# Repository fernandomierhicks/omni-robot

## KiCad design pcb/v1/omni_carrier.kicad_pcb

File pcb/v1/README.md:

# pcb/v1: Teensy 4.1 carrier (schematic draft, for review)

A two-layer breakout for the robot's Teensy 4.1: every header pin to a JST XH connector (2–6 pins), the CAN
transceivers as plug-in modules, and only the few parts a bare breakout can't do without. **Status (Nov 17): rev C
schematic for review; board placement study, not routed.** Every part is through-hole (Fernando solders by hand). Target fab:
OSH Park 2-layer (6 mil trace/space, 13 mil drill, 7 mil annular ring, 1.6 mm, ENIG, $5 per square inch for three).
How the board sits in the robot: [robot_block_diagram.html](robot_block_diagram.html) (published as an artifact).

| File | What |
| --- | --- |
| `tools/gen_sch.py` | **The source.** Generates the schematic, the project's symbol/footprint libraries and `nets.json` (the intended connectivity). Edit this, not the sheet, until the schematic is approved; after that KiCad is the source |
| `tools/check.py` | KiCad ERC; KiCad's netlist against `nets.json`; every Teensy pin against `firmware/lib/omni_fw/board_teensy41.h` (and the firmware changes this board needs); the review PDF |
| `omni_carrier.kicad_sch` / `.kicad_pro` | Open in KiCad 10 |
| `omni_carrier.kicad_sym`, `omni_carrier.pretty/` | Teensy 4.1 (outer 48 pins) and the SN65HVD230 module; the Teensy's 2 × 1x24 socket footprint, the Ø12 buzzer's (slotted pin 2) and J5's (1x4 socket + the ELRS receiver's outline and model) |
| `tools/elrs_model.py` → `models/elrs_receiver_on_J5.step` | The ELRS receiver on its male header, with its U.FL plug and T antenna, in J5's 3D frame (sizes from the vendor's pictures: VERIFY) |
| `tools/buzzer_model.py` → `models/buzzer_12085.step` | BZ1's 12085 buzzer (Ø12 × 8.5) in its footprint's 3D frame |
| `models/teensy_4_1.step`, `models/can.step`; `tools/paint_models.py` → `*_colour.step` | Fernando's Teensy 4.1 and SN65HVD230 module models (copied from `cad/v16/reference/electronics`, his SolidWorks parts; no colours), and the painted copies the footprints use |
| `tools/colour_step.py` → `out/omni_carrier_colour.step` | **The board for the CAD:** KiCad's STEP export, every face coloured (see Board, STEP) |
| `out/omni_carrier_schematic.pdf` | The sheet for review (A2) |
| `tools/gen_pcb.py` | Places the footprints on `omni_carrier.kicad_pcb` (placement study; runs in KiCad's Python) |
| `robot_block_diagram.html` | The whole robot's power and signal block diagram |

```powershell
cd pcb/v1
& $env:USERPROFILE\.venvs\omni-robot-sim\Scripts\python.exe tools/gen_sch.py
& $env:USERPROFILE\.venvs\omni-robot-sim\Scripts\python.exe tools/check.py    # ERC 0, netlist = intent, firmware pins
```

## The robot around it (Fernando, Nov 17)

- **One main switch, which is also the e-stop**, right before the 30 A fuse: it cuts the whole robot, the computer
  and the Teensy included. There is no separate e-stop circuit, no contactor and no power board: the converters
  (19 V, 12 V, 5 V) are discrete DC/DC modules, and the four AK40-10s take the pack directly with no fuses of their
  own (they limit their own current).
- **One common ground** in the robot; CAN carries no ground wire.
- **USB:** the BMAX B8A Pro's four A and one C ports are all taken without a hub (D435, Teensy, servo adapter, lidar
  adapter, mic), and the GMKtec M5 Ultra has fewer. Proposed: a powered USB 2 hub on the 5 V rail for the lidar adapter,
  the mic and the servo adapter (plus spares); the D435 (USB 3) and the Teensy keep direct ports.

## Design (rev C)

- **Power: the Teensy runs from USB only.** +5V on the connectors is the Teensy's VIN (= VUSB, trace intact); +3V3 is
  its regulator (~250 mA for the BNO085, the CAN modules ≤ 20 mA each, the 3V3 LED and the spares).
- **Through-hole only:** standing 1/4 W resistors (2.54 mm pitch), disc and radial capacitors, a 2N7000 (TO-92), a
  1N4148 (DO-35), a 3 mm LED; the Teensy (2 × 1x24) and the CAN modules (1x6) in 0.1 in sockets.
- **CAN1 (J6: H, L):** the AK40-10s are daisy-chained in the harness. The SN65HVD230 module (U2, `components/can`;
  pins 3V3, GND, CTX, CRX, CANH, CANL) carries its own 120 Ω, terminating this end; **the far end of the chain needs
  the second 120 Ω** (harness or last motor). **CAN3 (J10: H, L):** reserved payload bus, U3 fitted when used.
- **IMU, the BNO085 board in `components/imu`:** J4 = VCC, GND; J3 = SCL, SDA, AD0, CS, INT, RST in the board's own
  order, so the cable runs straight. In SPI mode SCL is SCK (13), SDA is MISO (12), AD0 is MOSI (11) (BNO08x pin
  functions; VERIFY on the board). PS0/PS1 are tied high on the board; BOOTN is not wired.
- **Pack voltage: the INA226 (Nov 19, Fernando).** No divider on the board any more (it was J1 + 100k/10k on A17): the
  INA226 already sits on the pack's high side after the fuse, and its bus-voltage register reads the pack (0-36 V,
  1.25 mV steps, better than the divider through the Teensy's ADC). Pin 41 (A17) is a spare on J19. The 21 V stop now
  depends on I2C, so the firmware must treat a missing or stale INA226 reading as a low pack (fail safe). VERIFY on
  the module bought that its VBUS pin sees the pack (on some INA226 boards VBUS is tied to IN−, on others it is a
  separate pin to wire to it).
- **Buzzer (BZ1, on the board, Nov 18):** a 12085 passive magnetic buzzer (Ø12 × 8.5 mm, 42 Ω, 5 V;
  `components/buzzer`) soldered straight to the carrier, no lead. 2N7000 low-side switch with a 1N4148 flyback to
  +5V; firmware `tone()` drives it (a passive buzzer needs the square wave). About 120 mA peak from USB 5 V, ~60 mA
  average while sounding. Footprint `omni_carrier:Buzzer_D12_P6.5-7.6_Slot`: pin 1 = + (square pad, marked +), pin 2
  in a plated slot that takes either common pin pitch (6.5 or 7.6 mm). **VERIFY the pitch and + mark on the
  delivered buzzers.** The 2N7000 at 3.3 V gate is near its threshold; if the buzzer is quiet, swap Q1 for a
  logic-level TO-92 FET.
- **RGB status LED (J15: R, GND, G, B, Nov 18):** common cathode, driven straight from pins 28 (R), 29 (G), 5 (B)
  through the board's 330 / 100 / 100 Ω (~4 mA each at 3.3 V; VERIFY brightness on the LED chosen). J15 is in the
  LED's own leg order (R, cathode = the longest leg, G, B), so the LED can solder straight into J15's holes instead of
  the XH (2.50 vs 2.54 mm: 0.12 mm over the four legs) or sit on a lead. VERIFY the leg order on the LED bought.
- **NeoPixel strip (J20: +5V, DIN, GND):** driven straight from pin 35 (Serial8 TX, so WS2812Serial can update it
  without blocking the 1 kHz loop) through 330 Ω; Fernando has run strips on 3.3 V data. +5V here is USB, so short
  strips only (~10 pixels at modest brightness); a longer strip takes 5 V from the 5 V converter at the strip and only
  DIN + GND from here.
- **ELRS receiver (J5, on the board, Nov 18, Fernando):** the HPXGRC ELRS 2.4 GHz receiver
  (`components/radio receiver`: 20 × 11 mm, 0.8 g, four pads T R V G on one short edge, a U.FL and a 40 mm T
  antenna) plugs straight into the carrier, no lead: a straight male 1x4 header soldered into its pads (short pins
  up through the pads, the plastic under it) goes into **J5, a 1x4 2.54 mm female socket**. The receiver lies flat
  along the top edge, components up, 11 mm over the board (socket 8.5 + the header's plastic 2.5), its U.FL toward
  −x; nothing is placed under it (its outline is in J5's courtyard). Read from the G end its pads are G, V, R, T =
  J5's 1-4 (GND, 5 V, its RX ← Teensy TX2 (8), its TX → Teensy RX2 (7)). Footprint
  `omni_carrier:ELRS_Rx_Socket_1x04_P2.54mm` carries KiCad's socket model and the receiver's
  (`models/elrs_receiver_on_J5.step`, from `tools/elrs_model.py`). **VERIFY before ordering, with calipers: the pads'
  pitch (the vendor's pictures read 2.3-2.45 mm; a 2.54 header needs 2.54) and that the pads are plated through.**
  If they are not, the fallback is the receiver's own pre-soldered leads crimped into a 1x4 Dupont housing on the
  same socket. The antenna's 40 mm coax stands up from the U.FL in the CAD; route it upright, away from the computer
  and the converters.
- **Power monitors on I2C (pins 18/19):** J12 to the INA3221, J21 to the INA226, same bus; the modules' own pull-ups
  serve it. Both sit with the converters, on cables, so no rail current crosses the carrier.
- **Spares (J11, J16–J19):** every remaining header pin. Each spare signal has a 10k position (DNI by default) to its
  connector's bias net; a 3-pad solder jumper per connector sets the bias: pads 1-2 = pull-up to 3V3, 2-3 =
  pull-down. Fit only the resistors a signal needs (open-drain, floating inputs).

## Power monitoring

| Monitor | Measures | Shunt | Full scale |
| --- | --- | --- | --- |
| **INA226** (rated to 36 V), J21, set to 0x41 | **Robot total current** and **the pack voltage** (bus voltage), high side after the fuse | external 50 A / 75 mV (1.5 mΩ) | ~55 A; 36 V |
| INA3221 CH1, J12 | **Arm 12 V** (1 A typical, 6.7 A peak est) | 10 mΩ 2512 (replace R100) | 16.4 A |
| INA3221 CH2 | **Computer 19 V** (1.6 A typical, 3.4 A peak) | 20 mΩ 2512 | 8.2 A |
| INA3221 CH3 | 5 V rail (display, audio, USB hub) | 50 mΩ 2512 | 3.3 A |

**Why the total isn't on the INA3221:** its inputs are rated 0–26 V absolute maximum and a full 6S pack is 25.2 V,
so regen or a charger spike can exceed it, and its module's traces aren't for 20 A bursts. The INA226 (GY-INA226
class modules, 36 V) on an external shunt takes the pack current, and its bus voltage is the pack voltage.

## Connectors

| Ref | Pins | 1 | 2 | 3 | 4 | 5 | 6 |
| --- | --- | --- | --- | --- | --- | --- | --- |
| J3 BNO085 data | XH6 | SCL = SCK (13) | SDA = MISO (12) | AD0 = MOSI (11) | CS (10) | INT (9) | RST (6) |
| J4 BNO085 power | XH2 | VCC (3V3) | GND | | | | |
| J5 ELRS (receiver plugged in) | 1x4 2.54 socket | GND (rx G) | 5 V (rx V) | TX2 (8) → rx R | RX2 (7) ← rx T | | |
| J6 CAN1 | XH2 | CAN H | CAN L | | | | |
| J10 CAN3 | XH2 | CAN H | CAN L | | | | |
| J11 spare | XH6 | GND | 3V3 | 0 RX1 | 1 TX1 | 27 | 40 (A16) |
| J12 INA3221 | XH4 | 3V3 (VS) | GND | SDA (18) | SCL (19) | | |
| J13 camera / sync | XH4 | GND | CAM_TRIG (24) | SYNC_OUT (25) | CAM_STROBE (26) | | |
| J15 RGB LED | XH4 | R (28) | GND | G (29) | B (5) | | |
| J16 spare | XH6 | GND | 3V3 | 14 TX3 | 15 RX3 | 16 RX4 | 17 TX4 |
| J17 spare | XH6 | GND | 3V3 | 2 | 3 | 20 TX5 | 21 RX5 |
| J18 spare | XH6 | GND | 32 | 33 | 36 | 37 | 38 (A14) |
| J19 spare | XH5 | 3V3 | GND | 39 (A15) | 34 | 41 (A17) | |
| J20 NeoPixel | XH3 | 5 V | DIN (35) | GND | | | |
| J21 INA226 | XH4 | 3V3 (VS) | GND | SDA (18) | SCL (19) | | |

## Board: placement study (Nov 17; routing study below)

`tools/gen_pcb.py` (KiCad's own Python: `"C:\Program Files\KiCad\10.0\bin\python.exe" tools/gen_pcb.py`, after
`tools/check.py`) builds `omni_carrier.kicad_pcb` from the netlist, with each footprint linked to its symbol (so
KiCad's Update PCB from Schematic still works) and OSH Park's 2-layer rules. Renders: `out/placement_top.png`,
`out/placement_iso.png`. KiCad DRC: no courtyard overlaps; the open items are the unrouted connections and
reference-text placement.

- **Size: 102 × 62 mm** (9.8 sq in, about $49 for three at OSH Park; 7 mm wider than the earlier 95 × 62 for the
  corner holes, Nov 18). The CAD's carrier envelope (100 × 65 mm) adapts to it; it sits
  on top of the power stack (`cad/v15/tools/upper.py` BLOCK `mcu`, centred at robot (37, −143.5), z 252.5).
- **Edges follow the cables in `cad/v15`:** board x = robot +x, board y down = robot −y.
  - **Left (robot −x, toward the computer):** the Teensy's USB end.
  - **Top (robot +y, toward the IMU at (32, −40) and the robot's centre):** J4, J3 IMU; J20 NeoPixel; J15 RGB (their
    resistors under them); then J5 at the right end (pin 1 at board (80.2, 2.5)) with the ELRS receiver lying over
    the strip x 61.1-82.0, y 0.5-12.1 above the Teensy's end. BZ1 (the buzzer) in the top-right corner below it
    (courtyards 0.8 mm apart); its Q1, R12, D1 between C6 and J19.
  - **Bottom (robot −y, toward the motor leads' fin slot and the converters below):** J6 CAN1, J10 CAN3, J12 INA3221,
    J21 INA226, J13 camera/sync (J1 pack sense gone, Nov 19).
  - **Right (robot +x):** spares J11, J16, J17, each with its bias column, 7 mm in from the edge (the corner holes);
    J18 on the left under the Teensy, J19 inside. The top and bottom rows start 7 mm in from the left corners.
- **Mounting (Fernando, Nov 18): four M3 holes at the corners**, 3.5 mm in from both edges: board (3.5, 3.5),
  (98.5, 3.5), (3.5, 58.5), (98.5, 58.5), 95 × 55 mm apart; each corner kept clear 7 mm for the hole and an M3 pan
  head (Ø6.5). They replace the earlier holes inside the board. The CAD adapts to them (its tray / posts are not
  drawn yet; M3 into Ø2.8 pilots).
- **Height over the board's top (VERIFY against the CAD's 25 mm envelope; from the models, Nov 19):** the Teensy on
  its 8.5 mm sockets 15.9 mm (its headers' plastic sits on the sockets, so its board is at 12.1-13.7); each CAN module
  standing in its 1x6 socket 25.7 mm (on a 2.5 mm header; standing up needs a right-angle header, a straight one
  lays it flat); an XH plug with its wires about 20 mm; the buzzer 8.5 mm; the ELRS receiver about 14.5 mm (its U.FL
  plug), its antenna about 52 mm as drawn (upright).
- **3D models (Nov 19):** U1 = KiCad's two 1x24 sockets + Fernando's Teensy 4.1 seated on them; U2 / U3 = the
  SN65HVD230 module standing in its socket, pin holes down (added by `gen_pcb.py`, `gen_sch.CAN_MODEL`); BZ1 = the
  12085; J5 = the receiver. The Teensy and CAN models come from his SolidWorks parts without colours;
  `tools/paint_models.py` paints copies (Teensy: green board, black parts and header plastic, gold pins, silver
  micro-B; CAN: blue board, black transceiver) so KiCad's 3D view shows them.
- **STEP for the CAD: `out/omni_carrier_colour.step`** (`tools/colour_step.py`, omni-robot-sim interpreter, after
  `gen_pcb.py`): KiCad's export (board, pads, every model) rewritten as one part with a colour on every face, the
  form SolidWorks shows (it ignores KiCad's solid colours): the board OSH Park purple, the pads gold, each model its
  own colours. KiCad's frame: x 0..102, y −62..0, the board's underside at z 0. The plain export it starts from is
  `out/omni_carrier.step`. `cad/v15` / `v16` read an older copy (`reference/electronics/omni_carrier_v1.step`,
  without the Teensy, CAN modules and buzzer, which the CAD adds itself): replacing it means dropping those.
- **Fab rules in the project file:** `gen_pcb.py` writes OSH Park's limits (0.152 mm track / space, 0.33 mm drill, 0.178 mm
  ring, 0.381 mm copper to edge) and the net classes (signals 0.2 mm, power +5V / +3V3 / GND 0.5 mm, 0.2 mm clearance,
  vias 0.8 / 0.4 mm) into `omni_carrier.kicad_pro`; KiCad keeps a board's rules there, not in the board file.
  Q1 is on `TO-92_Inline_Wide` (2.54 mm pitch; spread the 2N7000's legs): the 1.27 mm footprint's copper ring is 0.15 mm.

## Preliminary routing (Nov 19): two layers work

`tools/route.py` (KiCad's Python, after `gen_pcb.py`) autoroutes the placement with Freerouting 2.5.0 and writes
**`omni_carrier_routed.kicad_pcb`** (a study; the placement board stays the source until the layout is approved).
It predates the Nov 19 changes (J1 gone, J19 an XH5): rerun it with KiCad closed.
Result: **every connection routed on two layers**, about 3.7 m of track and 24 vias, GND poured on both sides; KiCad
DRC against the OSH Park rules: 0 unconnected, no clearance, width or edge errors (left: silkscreen text overlaps from the
placement, and 5 GND pads whose pour thermal has one spoke instead of two: they are also on GND tracks). Renders:
`out/route/routed_top.png`, `routed_bottom.png`; DRC `out/route/drc_routed.json`.

- The router only finishes this board with its automatic neckdown on: it squeezes tracks to 0.12-0.19 mm between
  pads (with it off it stalls at 34-37 unrouted, at 0.25 or 0.2 mm tracks). `route.py` widens every track under
  0.16 mm back to 0.16 after import; the router kept 0.2 mm around them, so they keep >= 0.18 mm to their neighbours.
- An autorouted layout is a feasibility answer, not the board to order: hand-tidy or reroute it once the placement and
  the CAD heights are settled (long detours round the Teensy, a few vias that a hand route would not need).
- Tools (not in the repo; download and verify the checksums): `freerouting-2.5.0.jar` (github.com/freerouting/freerouting
  releases; the v2.5.0 native `freerouting-cli.exe` crashes on Windows) on a Java 25 runtime (Temurin 25 JRE zip;
  the jar is class version 69). `FREEROUTING_JAR=<jar> JAVA=<jre>\bin\java.exe "C:\Program Files\KiCad\10.0\bin\python.exe"
  tools/route.py`. Do not run it with the project open in KiCad: it clears KiCad's project lock file.

## Firmware to change for this board (`tools/check.py` lists them)

`board_teensy41.h`: the e-stop input (pin 35) goes, as the main switch now removes all power (left as it is, pin 35
would read 1 = stop), and 35 becomes the NeoPixel data; pin 5 (was BNO_WAKE) → LED_B, 29 (was BNO_PS1) → LED_G,
28 LED → LED_R; 27 (BNO_BOOTN), 34, 39 (I_BUS), 40 (V_12) and 41 (V_BUS) become spares. `main.cpp`: an INA3221 +
INA226 reader on Wire, the INA226's bus voltage replacing the A17 divider (`V_BUS_DIVIDER`) as `v_bus`, a missing or
stale reading counting as low; RGB and NeoPixel status; stop driving the BNO085's WAKE/PS1/BOOTN.

## Open for the review

- The main switch: it must carry the whole robot (20 A bursts, 30 A fuse) and the converters' inrush. Few latching
  e-stop buttons are rated for that much DC, so pick a rated battery-disconnect switch or let the button drive a
  high-current anti-spark switch. It also drops the computer without a shutdown.
- The INA226's address: set it to 0x41 (A0 to VS); both modules default to 0x40.
- The CAD changes to fit it (blue sky, not drawn; block diagram page, "Blue sky: power down, logic in the middle"):
  the power parts move to the first floor's centre over the battery (the drive leads stay down there); the carrier
  sits in the open middle of floor 2 between the arm and the bin, plugs up; the computer moves under the bin; one
  slot beside the spine fin carries everything that climbs. Board size: as small as the layout allows (Fernando).
- The height of the CAN modules standing in their sockets (see Board).

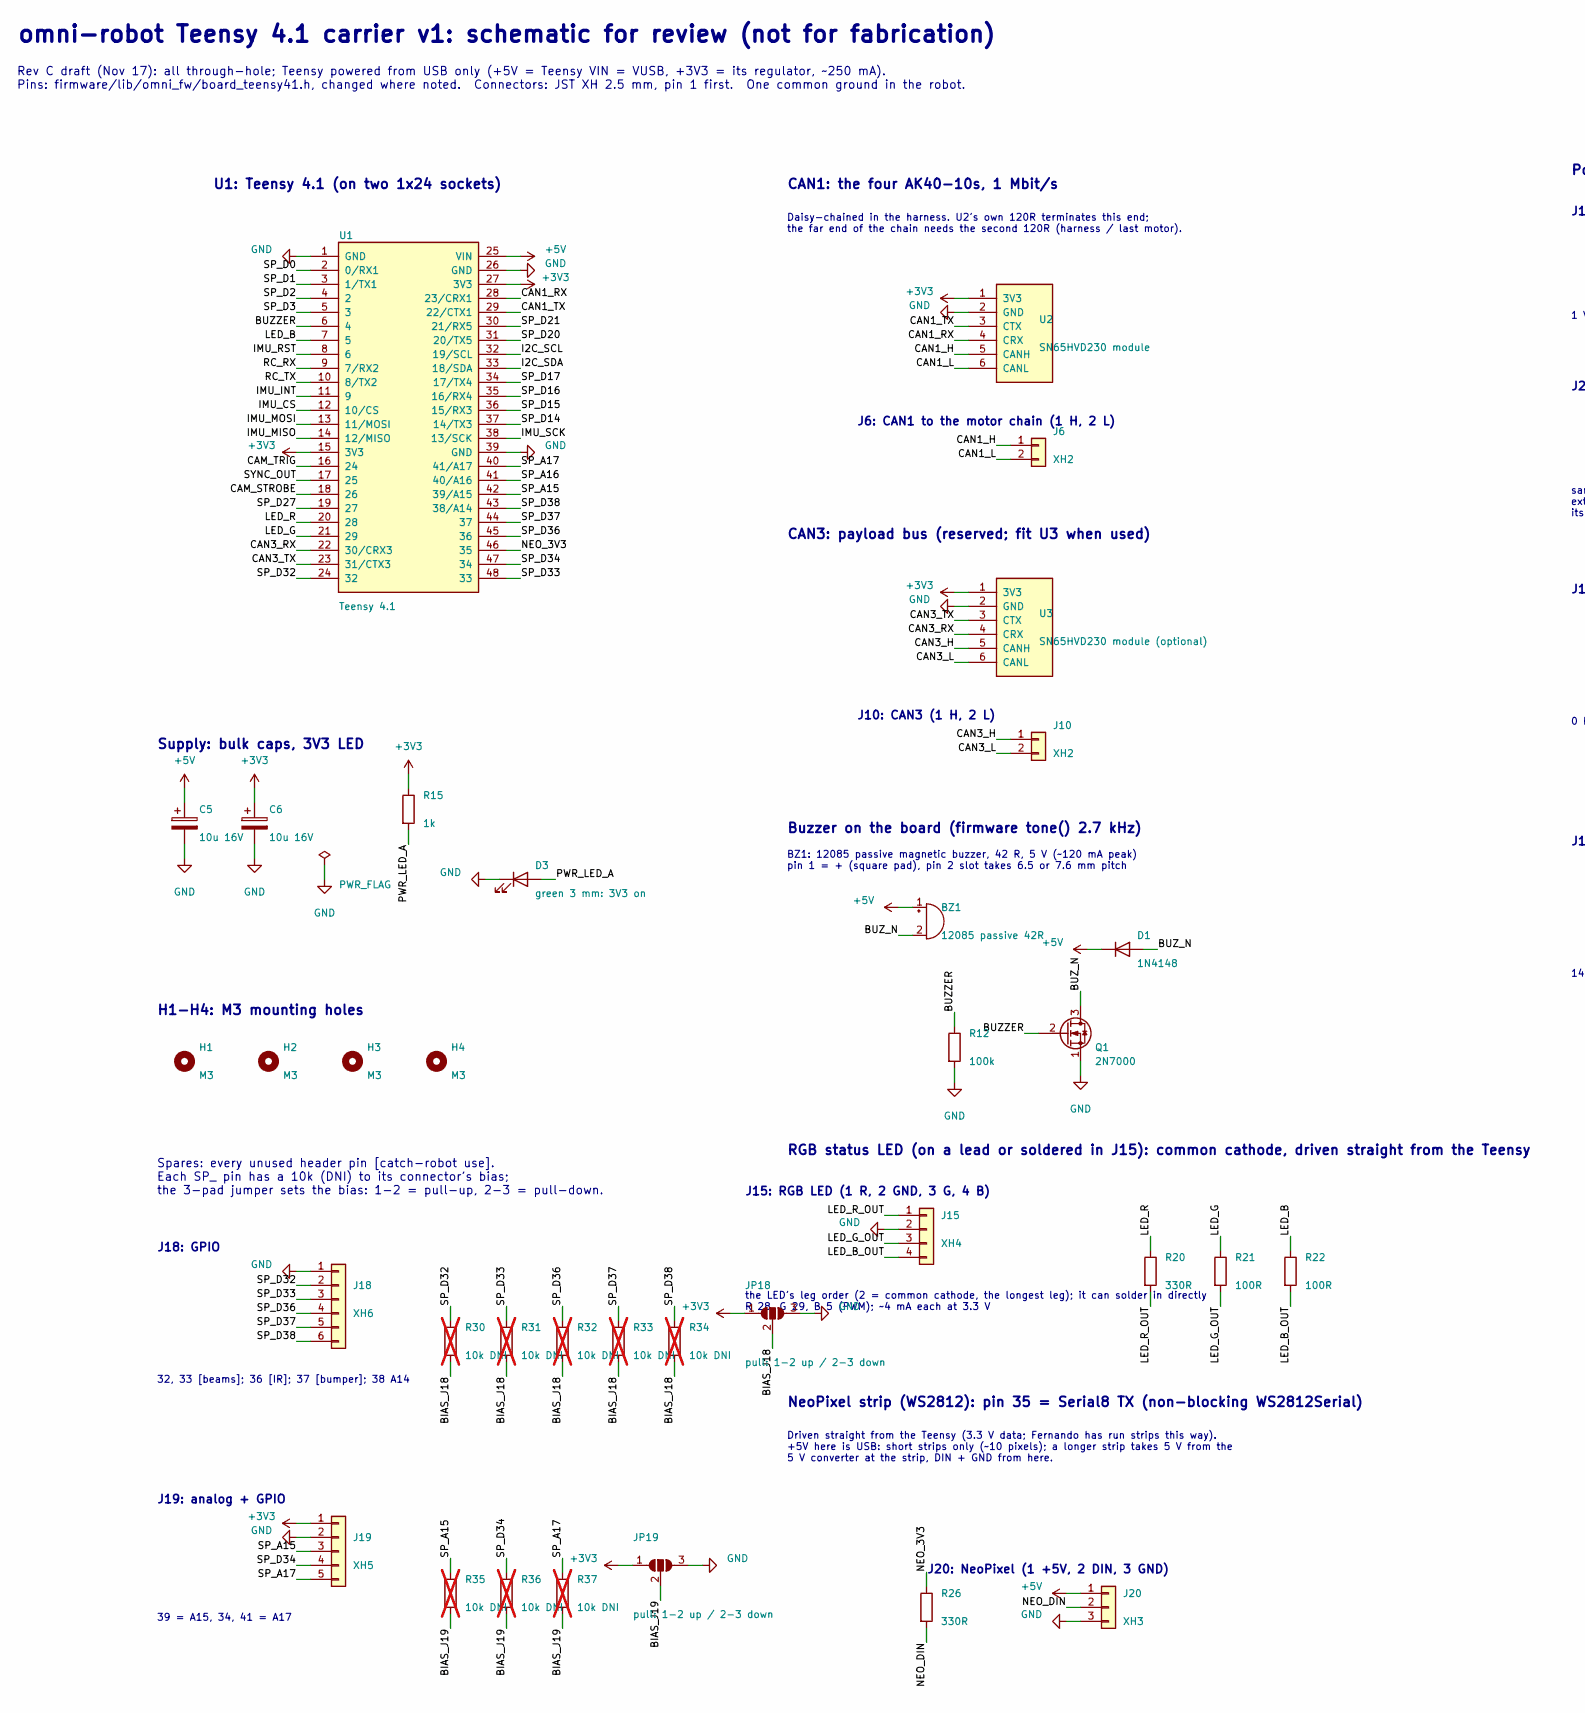
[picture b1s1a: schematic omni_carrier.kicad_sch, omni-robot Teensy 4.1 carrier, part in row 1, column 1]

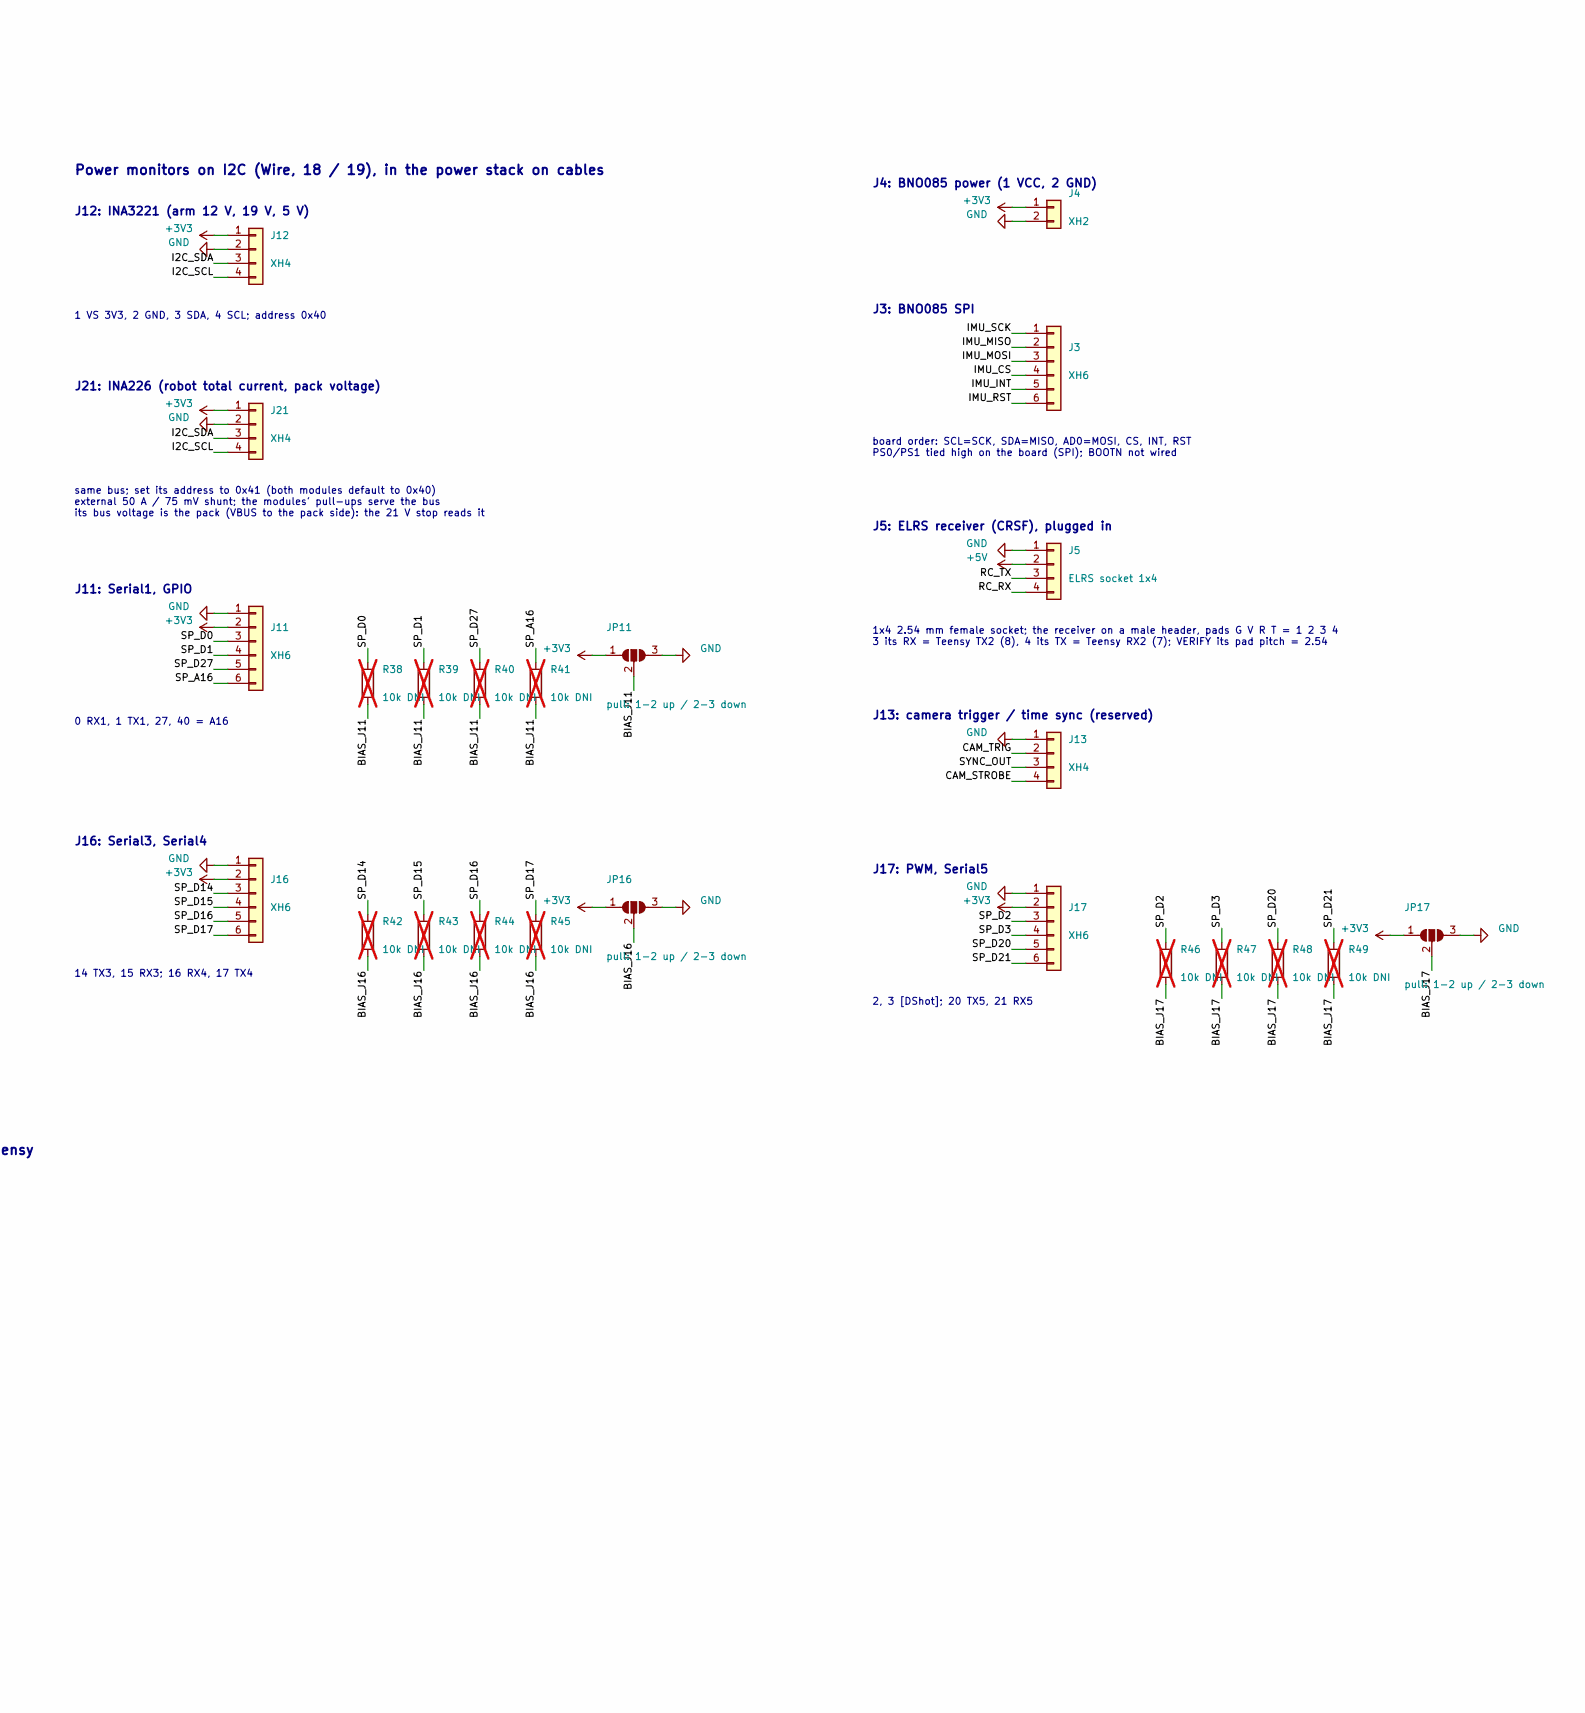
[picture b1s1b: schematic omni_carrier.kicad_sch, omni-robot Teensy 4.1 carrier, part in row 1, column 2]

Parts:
BZ1: 12085 passive 42R; Buzzer_D12_P6.5-7.6_Slot
C5, C6: 10u 16V; CP_Radial_D5.0mm_P2.00mm
D1: 1N4148; D_DO-35_SOD27_P2.54mm_Vertical_AnodeUp
D3: green 3 mm: 3V3 on; LED_D3.0mm
H1, H2, H3, H4: M3; MountingHole_3.2mm_M3
J3, J11, J16, J17, J18: XH6; JST_XH_B6B-XH-A_1x06_P2.50mm_Vertical
J4, J6, J10: XH2; JST_XH_B2B-XH-A_1x02_P2.50mm_Vertical
J5: ELRS socket 1x4; ELRS_Rx_Socket_1x04_P2.54mm
J12, J13, J15, J21: XH4; JST_XH_B4B-XH-A_1x04_P2.50mm_Vertical
J19: XH5; JST_XH_B5B-XH-A_1x05_P2.50mm_Vertical
J20: XH3; JST_XH_B3B-XH-A_1x03_P2.50mm_Vertical
JP11, JP16, JP17, JP18, JP19: pull: 1-2 up / 2-3 down; SolderJumper-3_P1.3mm_Open_RoundedPad1.0x1.5mm
Q1: 2N7000; TO-92_Inline_Wide
R12: 100k; R_Axial_DIN0207_L6.3mm_D2.5mm_P2.54mm_Vertical
R15: 1k; R_Axial_DIN0207_L6.3mm_D2.5mm_P2.54mm_Vertical
R20, R26: 330R; R_Axial_DIN0207_L6.3mm_D2.5mm_P2.54mm_Vertical
R21, R22: 100R; R_Axial_DIN0207_L6.3mm_D2.5mm_P2.54mm_Vertical
R30, R31, R32, R33, R34, R35, R36, R37, R38, R39, R40, R41, R42, R43, R44, R45, R46, R47, R48, R49: 10k DNI; R_Axial_DIN0207_L6.3mm_D2.5mm_P2.54mm_Vertical; not fitted
U1: Teensy 4.1; Teensy41_Socket
U2: SN65HVD230 module; PinSocket_1x06_P2.54mm_Vertical
U3: SN65HVD230 module (optional); PinSocket_1x06_P2.54mm_Vertical

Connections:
+3V3: C6.1, J4.1, J11.2, J12.1, J16.2, J17.2, J19.1, J21.1, JP11.1 (A), JP16.1 (A), JP17.1 (A), JP18.1 (A), JP19.1 (A), R15.1, U1.15 (3V3), U1.27 (3V3), U2.1 (3V3), U3.1 (3V3)
+5V: BZ1.1 (+), C5.1, D1.1 (K), J5.2, J20.1, U1.25 (VIN)
/BIAS_J11: JP11.2 (C), R38.2, R39.2, R40.2, R41.2
/BIAS_J16: JP16.2 (C), R42.2, R43.2, R44.2, R45.2
/BIAS_J17: JP17.2 (C), R46.2, R47.2, R48.2, R49.2
/BIAS_J18: JP18.2 (C), R30.2, R31.2, R32.2, R33.2, R34.2
/BIAS_J19: JP19.2 (C), R35.2, R36.2, R37.2
/BUZZER: Q1.2 (G), R12.1, U1.6 (4)
/BUZ_N: BZ1.2 (-), D1.2 (A), Q1.3 (D)
/CAM_STROBE: J13.4, U1.18 (26)
/CAM_TRIG: J13.2, U1.16 (24)
/CAN1_H: J6.1, U2.5 (CANH)
/CAN1_L: J6.2, U2.6 (CANL)
/CAN1_RX: U1.28 (23/CRX1), U2.4 (CRX)
/CAN1_TX: U1.29 (22/CTX1), U2.3 (CTX)
/CAN3_H: J10.1, U3.5 (CANH)
/CAN3_L: J10.2, U3.6 (CANL)
/CAN3_RX: U1.22 (30/CRX3), U3.4 (CRX)
/CAN3_TX: U1.23 (31/CTX3), U3.3 (CTX)
/I2C_SCL: J12.4, J21.4, U1.32 (19/SCL)
/I2C_SDA: J12.3, J21.3, U1.33 (18/SDA)
/IMU_CS: J3.4, U1.12 (10/CS)
/IMU_INT: J3.5, U1.11 (9)
/IMU_MISO: J3.2, U1.14 (12/MISO)
/IMU_MOSI: J3.3, U1.13 (11/MOSI)
/IMU_RST: J3.6, U1.8 (6)
/IMU_SCK: J3.1, U1.38 (13/SCK)
/LED_B: R22.1, U1.7 (5)
/LED_B_OUT: J15.4, R22.2
/LED_G: R21.1, U1.21 (29)
/LED_G_OUT: J15.3, R21.2
/LED_R: R20.1, U1.20 (28)
/LED_R_OUT: J15.1, R20.2
/NEO_3V3: R26.1, U1.46 (35)
/NEO_DIN: J20.2, R26.2
/PWR_LED_A: D3.2 (A), R15.2
/RC_RX: J5.4, U1.9 (7/RX2)
/RC_TX: J5.3, U1.10 (8/TX2)
/SP_A15: J19.3, R35.1, U1.42 (39/A15)
/SP_A16: J11.6, R41.1, U1.41 (40/A16)
/SP_A17: J19.5, R37.1, U1.40 (41/A17)
/SP_D0: J11.3, R38.1, U1.2 (0/RX1)
/SP_D1: J11.4, R39.1, U1.3 (1/TX1)
/SP_D2: J17.3, R46.1, U1.4 (2)
/SP_D3: J17.4, R47.1, U1.5 (3)
/SP_D14: J16.3, R42.1, U1.37 (14/TX3)
/SP_D15: J16.4, R43.1, U1.36 (15/RX3)
/SP_D16: J16.5, R44.1, U1.35 (16/RX4)
/SP_D17: J16.6, R45.1, U1.34 (17/TX4)
/SP_D20: J17.5, R48.1, U1.31 (20/TX5)
/SP_D21: J17.6, R49.1, U1.30 (21/RX5)
/SP_D27: J11.5, R40.1, U1.19 (27)
/SP_D32: J18.2, R30.1, U1.24 (32)
/SP_D33: J18.3, R31.1, U1.48 (33)
/SP_D34: J19.4, R36.1, U1.47 (34)
/SP_D36: J18.4, R32.1, U1.45 (36)
/SP_D37: J18.5, R33.1, U1.44 (37)
/SP_D38: J18.6, R34.1, U1.43 (38/A14)
/SYNC_OUT: J13.3, U1.17 (25)
GND: C5.2, C6.2, D3.1 (K), J4.2, J5.1, J11.1, J12.2, J13.1, J15.2, J16.1, J17.1, J18.1, J19.2, J20.3, J21.2, JP11.3 (B), JP16.3 (B), JP17.3 (B), JP18.3 (B), JP19.3 (B), Q1.1 (S), R12.2, U1.1 (GND), U1.26 (GND), U1.39 (GND), U2.2 (GND), U3.2 (GND)

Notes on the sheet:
omni-robot Teensy 4.1 carrier v1: schematic for review (not for fabrication)
Rev C draft (Nov 17): all through-hole; Teensy powered from USB only (+5V = Teensy VIN = VUSB, +3V3 = its regulator, ~250 mA). Pins: firmware/lib/omni_fw/board_teensy41.h, changed where noted. Connectors: JST XH 2.5 mm, pin 1 first. One common ground in the robot.
U1: Teensy 4.1 (on two 1x24 sockets)
Supply: bulk caps, 3V3 LED
H1-H4: M3 mounting holes
Spares: every unused header pin [catch-robot use]. Each SP_ pin has a 10k (DNI) to its connector's bias; the 3-pad jumper sets the bias: 1-2 = pull-up, 2-3 = pull-down.
J18: GPIO
32, 33 [beams]; 36 [IR]; 37 [bumper]; 38 A14
J19: analog + GPIO
39 = A15, 34, 41 = A17
CAN1: the four AK40-10s, 1 Mbit/s
Daisy-chained in the harness. U2's own 120R terminates this end; the far end of the chain needs the second 120R (harness / last motor).
J6: CAN1 to the motor chain (1 H, 2 L)
CAN3: payload bus (reserved; fit U3 when used)
J10: CAN3 (1 H, 2 L)
Buzzer on the board (firmware tone() 2.7 kHz)
BZ1: 12085 passive magnetic buzzer, 42 R, 5 V (~120 mA peak) pin 1 = + (square pad), pin 2 slot takes 6.5 or 7.6 mm pitch
RGB status LED (on a lead or soldered in J15): common cathode, driven straight from the Teensy
J15: RGB LED (1 R, 2 GND, 3 G, 4 B)
the LED's leg order (2 = common cathode, the longest leg); it can solder in directly R 28, G 29, B 5 (PWM); ~4 mA each at 3.3 V
NeoPixel strip (WS2812): pin 35 = Serial8 TX (non-blocking WS2812Serial)
Driven straight from the Teensy (3.3 V data; Fernando has run strips this way). +5V here is USB: short strips only (~10 pixels); a longer strip takes 5 V from the 5 V converter at the strip, DIN + GND from here.
J20: NeoPixel (1 +5V, 2 DIN, 3 GND)
Power monitors on I2C (Wire, 18 / 19), in the power stack on cables
J12: INA3221 (arm 12 V, 19 V, 5 V)
1 VS 3V3, 2 GND, 3 SDA, 4 SCL; address 0x40
J21: INA226 (robot total current, pack voltage)
same bus; set its address to 0x41 (both modules default to 0x40) external 50 A / 75 mV shunt; the modules' pull-ups serve the bus its bus voltage is the pack (VBUS to the pack side): the 21 V stop reads it
J11: Serial1, GPIO
0 RX1, 1 TX1, 27, 40 = A16
J16: Serial3, Serial4
14 TX3, 15 RX3; 16 RX4, 17 TX4
J4: BNO085 power (1 VCC, 2 GND)
J3: BNO085 SPI
board order: SCL=SCK, SDA=MISO, AD0=MOSI, CS, INT, RST PS0/PS1 tied high on the board (SPI); BOOTN not wired
J5: ELRS receiver (CRSF), plugged in
1x4 2.54 mm female socket; the receiver on a male header, pads G V R T = 1 2 3 4 3 its RX = Teensy TX2 (8), 4 its TX = Teensy RX2 (7); VERIFY its pad pitch = 2.54
J13: camera trigger / time sync (reserved)
J17: PWM, Serial5
2, 3 [DShot]; 20 TX5, 21 RX5

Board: 2 copper layers, 59 parts (0 on the bottom side), 60 nets, no tracks yet.

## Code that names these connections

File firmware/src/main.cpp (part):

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static volatile bool g_strobe_new = false;
static void strobe_isr() {
    uint32_t now = micros();
    if (digitalReadFast(pin::CAM_STROBE)) {
        g_strobe_rise32 = now;
    } else {
        g_strobe_width = now - g_strobe_rise32;
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    pinMode(pin::ESTOP, INPUT_PULLUP);
    pinMode(pin::BUMPER_FRONT, INPUT_PULLUP);
    pinMode(pin::BUMPER_REAR, INPUT_PULLUP);
    pinMode(pin::BUZZER, OUTPUT);
    pinMode(pin::LED, OUTPUT);
    analogWriteFrequency(pin::IR_EMIT, 38000);   // the beams' receivers are 38 kHz demodulators
    analogWrite(pin::IR_EMIT, 128);
    analogReadResolution(12);
    g_bno.begin();
    g_sync.pin = pin::SYNC_OUT;
    g_cam.pin = pin::CAM_TRIG;
    g_cam.width_us = 20;
    pinMode(pin::SYNC_OUT, OUTPUT);
    pinMode(pin::CAM_TRIG, OUTPUT);
    pinMode(pin::CAM_STROBE, INPUT);
    attachInterrupt(digitalPinToInterrupt(pin::CAM_STROBE), strobe_isr, CHANGE);
    g_fw.init();
    g_servo.torque(true);
    watchdog_start();                            // last: setup's own waits don't count
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        case 7: if (tick % 20 == 7) g_servo.request_pos(); break;
        default: break;
    }
    if (out.buzzer) tone(pin::BUZZER, 2700, 50);
    digitalWriteFast(pin::LED, (out.led == fw::MODE_AUTO) ? ((tick / 250) & 1) : (out.led == fw::MODE_ESTOP));
}

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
